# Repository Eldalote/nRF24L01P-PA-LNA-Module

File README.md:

# nRF24L01P-PA-LNA-Module DO NOT USE

DO NOT USE THIS DESIGN!
When doing further projects with the nRF24L01p and PA LNA module, I came to the conclusion that I made some significant design errors in this design.
The current version of the design might function, maybe, but I know for sure that there are some errors.
For a better design look at my Drone project. Both the drone PCB and the remote PCB have this module integrated on the PCB.

PCB Design for nRF24L01P PA LNA module

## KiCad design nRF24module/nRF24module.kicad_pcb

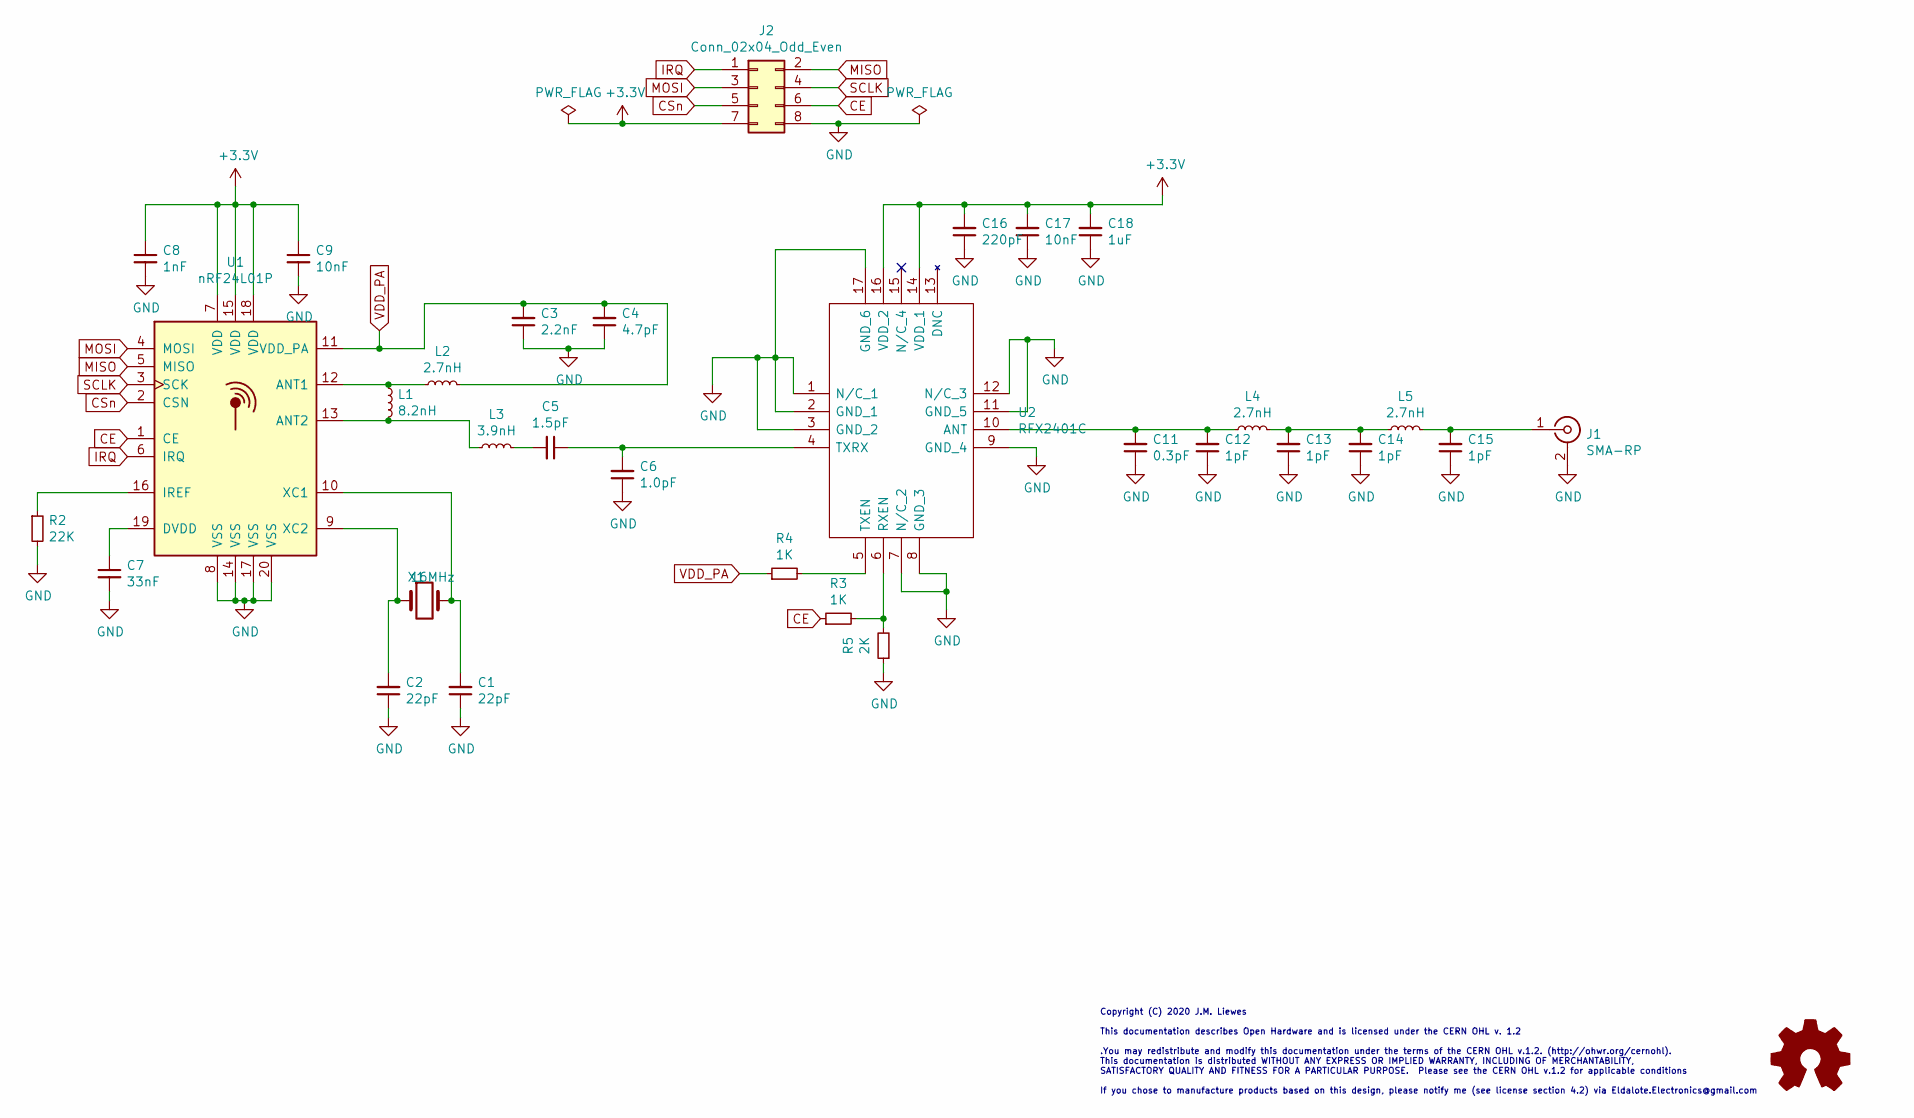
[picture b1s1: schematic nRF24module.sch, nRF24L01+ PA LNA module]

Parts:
C1, C2: 22pF; C_0402_1005Metric; LCSC C1555
C3: 2.2nF; C_0402_1005Metric; LCSC C1531
C4: 4.7pF; C_0402_1005Metric; LCSC C1569
C5: 1.5pF; C_0402_1005Metric; LCSC C1552
C6: 1.0pF; C_0402_1005Metric; LCSC C1550
C7: 33nF; C_0402_1005Metric; LCSC C1585
C8: 1nF; C_0402_1005Metric; LCSC C1523
C9, C17: 10nF; C_0402_1005Metric; LCSC C15195
C11: 0.3pF; C_0603_1608Metric; LCSC C170140
C12, C13, C14, C15: 1pF; C_0402_1005Metric; LCSC C1550
C16: 220pF; C_0402_1005Metric; LCSC C1530
C18: 1uF; C_0402_1005Metric; LCSC C52923
J1: SMA-RP; SMA_Samtec_SMA-J-P-X-ST-EM1_EdgeMount
J2: Conn_02x04_Odd_Even; PinHeader_2x04_P1.27mm_Vertical
L1: 8.2nH; L_0402_1005Metric; LCSC C16208
L2, L4, L5: 2.7nH; L_0402_1005Metric; LCSC C27123
L3: 3.9nH; L_0402_1005Metric; LCSC C14033
LOGO1: Logo_Open_Hardware_Small; OSHW-Logo2_7.3x6mm_SilkScreen
R2: 22K; R_0402_1005Metric; LCSC C25768
R3, R4: 1K; R_0402_1005Metric; LCSC C11702
R5: 2K; R_0402_1005Metric; LCSC C4109
U1: nRF24L01P; QFN-20-1EP_4x4mm_P0.5mm_EP2.5x2.5mm; LCSC C8791
U2: RFX2401C; QFN50P300X300X60-17N-D; Mouser Part Number 477-RFX2401C
X1: 16MHz; Crystal_SMD_3225-4Pin_3.2x2.5mm; LCSC C13738

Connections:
+3V3: C8.1, C9.1, C16.2, C17.2, C18.2, J2.7, U1.7 (VDD), U1.15 (VDD), U1.18 (VDD), U2.14 (VDD_1), U2.16 (VDD_2)
CE: J2.6, R3.1, U1.1 (CE)
CSn: J2.5, U1.2 (CSN)
IRQ: J2.1, U1.6 (IRQ)
MISO: J2.2, U1.5 (MISO)
MOSI: J2.3, U1.4 (MOSI)
unnamed: C2.2, U1.9 (XC2), X1.1
unnamed: C5.1, C6.2, U2.4 (TXRX)
unnamed: C5.2, L3.2
unnamed: C7.1, U1.19 (DVDD)
unnamed: C11.2, C12.2, L4.1, U2.10 (ANT)
unnamed: C13.2, C14.2, L4.2, L5.1
unnamed: C15.2, J1.1 (In), L5.2
unnamed: L1.1, L2.1, U1.12 (ANT1)
unnamed: L1.2, L3.1, U1.13 (ANT2)
unnamed: R2.1, U1.16 (IREF)
unnamed: R3.2, R5.2, U2.6 (RXEN)
unnamed: R4.2, U2.5 (TXEN)
SCLK: J2.4, U1.3 (SCK)
VDD_PA: C3.2, C4.2, L2.2, R4.1, U1.11 (VDD_PA)

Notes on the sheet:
Copyright (C) 2020 J.M. Liewes This documentation describes Open Hardware and is licensed under the CERN OHL v. 1.2 .You may redistribute and modify this documentation under the terms of the CERN OHL v.1.2. (http://ohwr.org/cernohl). This documentation is distributed WITHOUT ANY EXPRESS OR IMPLIED 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

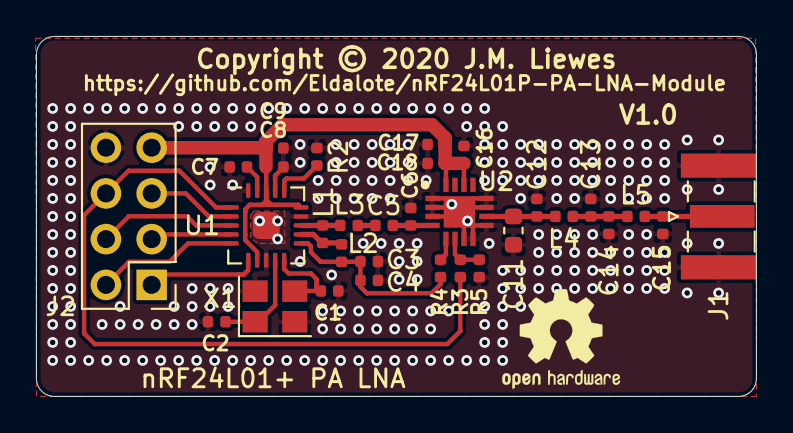
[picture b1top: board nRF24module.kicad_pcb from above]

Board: 2 copper layers, 40.0 x 20.0 mm, 32 parts (0 on the bottom side), 22 nets.

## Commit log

2020-08-21 Initial Commit with project
2020-08-21 Now with production files
2020-08-23 Update, with Licence added to files, and rerouted PCB, cleaned up some things. Tightened up components, placed traces neater, placed vias neater. Added OSHW logo. TODO: Make own logo and add that.
2020-08-28 Added licences, fixed crystal mistake
2020-09-16 Corrected crystal load capacitance.
2020-12-18 DO NOT USE DESIGN IN CURRENT STATE

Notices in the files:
nRF24module/nRF24module.kicad_pcb:
Copyright © 2020 J.M. Liewes
nRF24module/nRF24module.sch:
If you chose to manufacture products based on this design, please notify me (see license section 4.2) via Eldalote.Electronics@gmail.com
